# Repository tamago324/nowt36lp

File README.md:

# nowt36lp

horizon プラグインを使ってボトムプレートとトッププレートを生成した

## LICENSE

<br />この 作品 は <a rel="license" href="http://creativecommons.org/licenses/by/4.0/">クリエイティブ・コモンズ 表示 4.0 国際 ライセンス</a>の下に提供されています。

> 帰属—適切なクレジットを表示し、ライセンスへのリンクを提供し、変更が行われたかどうかを示す必要があります。

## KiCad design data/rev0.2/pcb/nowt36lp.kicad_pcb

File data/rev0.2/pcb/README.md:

## 発注するデータの作成方法

horizon のプラグインを使って、発注するためのデータを作成

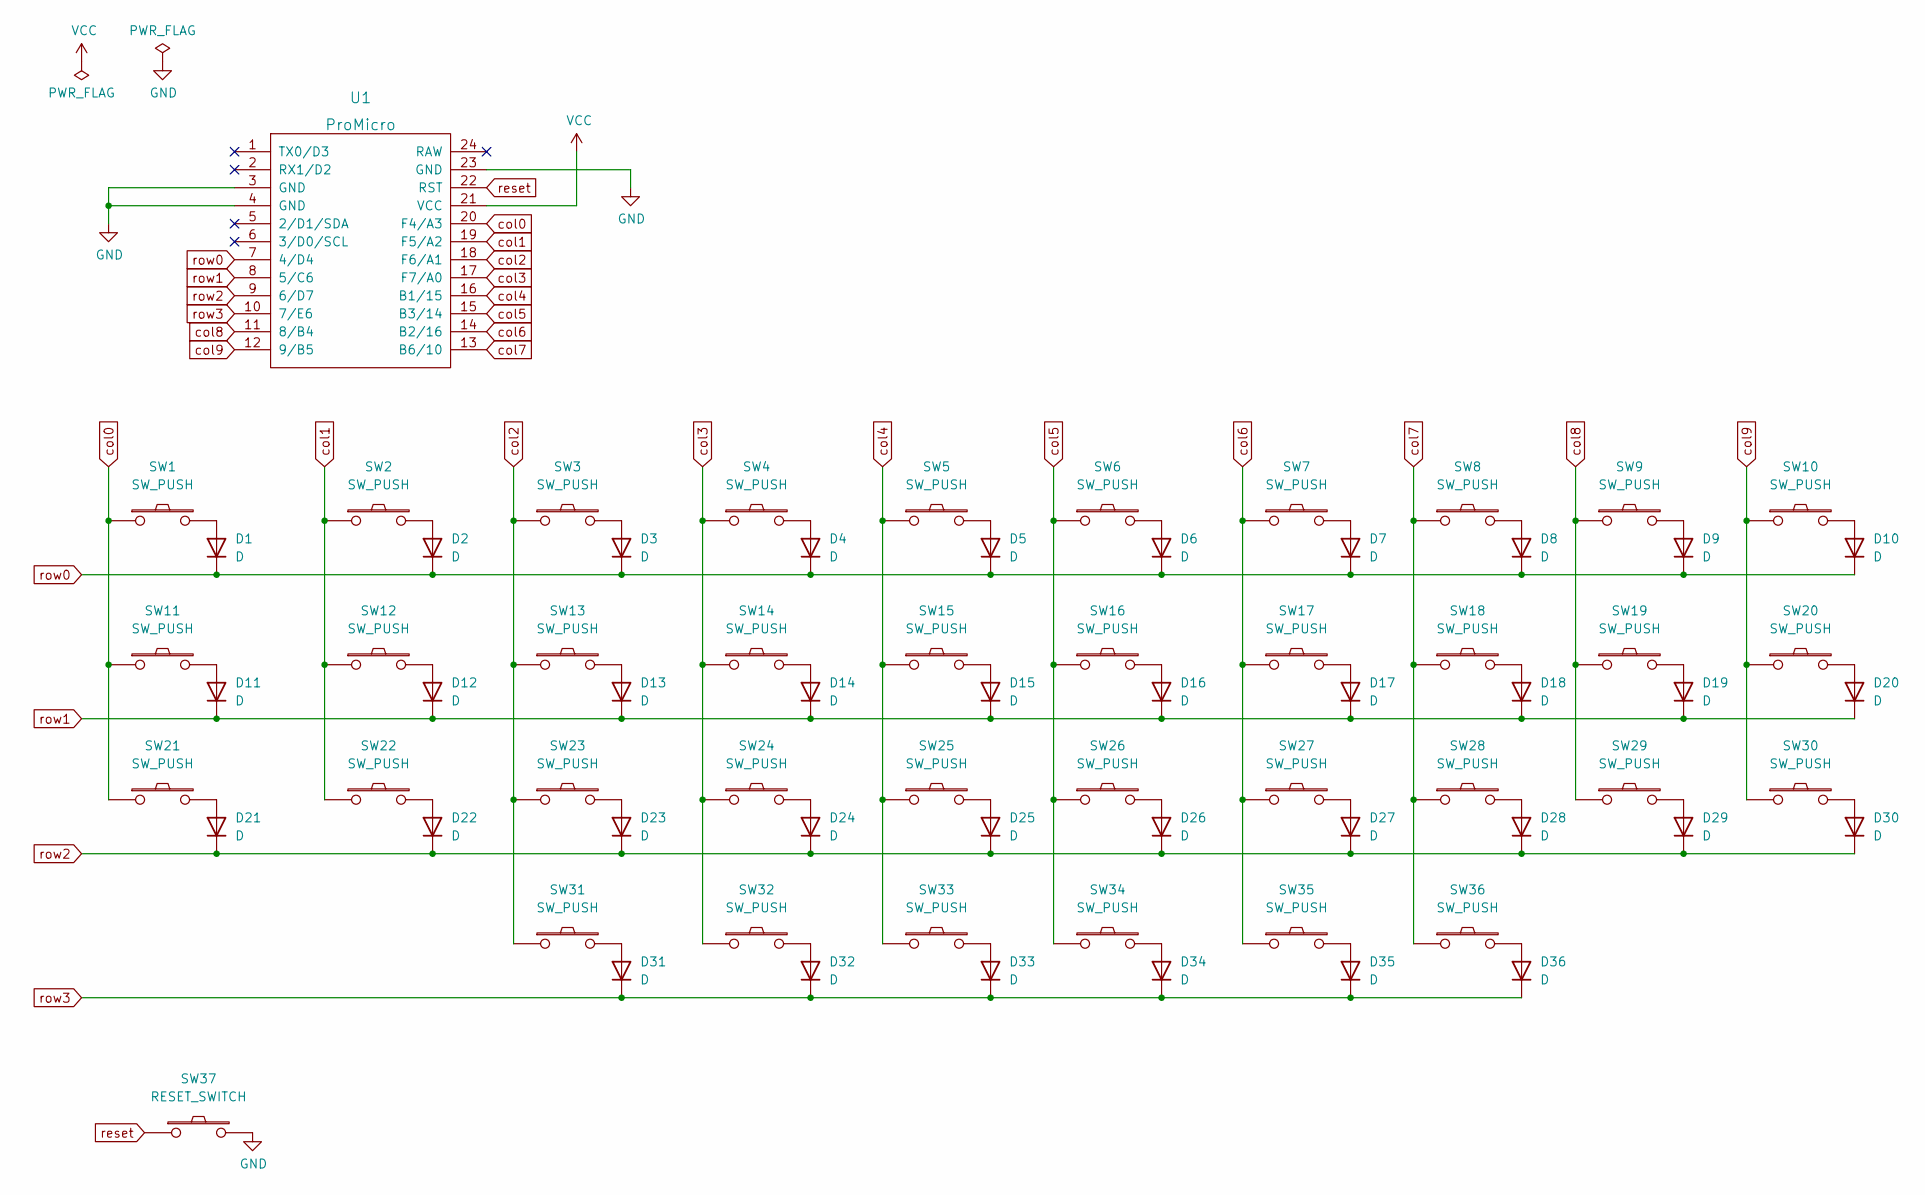
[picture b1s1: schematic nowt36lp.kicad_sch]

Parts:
D1, D2, D3, D4, D5, D6, D7, D8, D9, D10, D11, D12, D13, D14, D15, D16, D17, D18, D19, D20, D21, D22, D23, D24, D25, D26, D27, D28, D29, D30, D31, D32, D33, D34, D35, D36: D; Diode_SMD
SW1, SW2, SW3, SW4, SW5, SW6, SW7, SW8, SW9, SW10, SW11, SW12, SW13, SW14, SW15, SW16, SW17, SW18, SW19, SW20, SW21, SW22, SW23, SW24, SW25, SW26, SW27, SW28, SW29, SW30, SW31, SW32, SW33, SW34, SW35, SW36: SW_PUSH; SW_Choc
SW37: RESET_SWITCH; TVAF17-WFC-R_mods
U1: ProMicro; ProMicro_v3.5_mods

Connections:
GND: SW37.2, U1.3 (GND), U1.4 (GND), U1.23 (GND)
unnamed: D1.2 (A), SW1.2
unnamed: D2.2 (A), SW2.2
unnamed: D3.2 (A), SW3.2
unnamed: D4.2 (A), SW4.2
unnamed: D5.2 (A), SW5.2
unnamed: D6.2 (A), SW6.2
unnamed: D7.2 (A), SW7.2
unnamed: D8.2 (A), SW8.2
unnamed: D9.2 (A), SW9.2
unnamed: D10.2 (A), SW10.2
unnamed: D11.2 (A), SW11.2
unnamed: D12.2 (A), SW12.2
unnamed: D13.2 (A), SW13.2
unnamed: D14.2 (A), SW14.2
unnamed: D15.2 (A), SW15.2
unnamed: D16.2 (A), SW16.2
unnamed: D17.2 (A), SW17.2
unnamed: D18.2 (A), SW18.2
unnamed: D19.2 (A), SW19.2
unnamed: D20.2 (A), SW20.2
unnamed: D21.2 (A), SW21.2
unnamed: D22.2 (A), SW22.2
unnamed: D23.2 (A), SW23.2
unnamed: D24.2 (A), SW24.2
unnamed: D25.2 (A), SW25.2
unnamed: D26.2 (A), SW26.2
unnamed: D27.2 (A), SW27.2
unnamed: D28.2 (A), SW28.2
unnamed: D29.2 (A), SW29.2
unnamed: D30.2 (A), SW30.2
unnamed: D31.2 (A), SW31.2
unnamed: D32.2 (A), SW32.2
unnamed: D33.2 (A), SW33.2
unnamed: D34.2 (A), SW34.2
unnamed: D35.2 (A), SW35.2
unnamed: D36.2 (A), SW36.2
VCC: U1.21 (VCC)
col0: SW1.1, SW11.1, SW21.1, U1.20 (F4/A3)
col1: SW2.1, SW12.1, SW22.1, U1.19 (F5/A2)
col2: SW3.1, SW13.1, SW23.1, SW31.1, U1.18 (F6/A1)
col3: SW4.1, SW14.1, SW24.1, SW32.1, U1.17 (F7/A0)
col4: SW5.1, SW15.1, SW25.1, SW33.1, U1.16 (B1/15)
col5: SW6.1, SW16.1, SW26.1, SW34.1, U1.15 (B3/14)
col6: SW7.1, SW17.1, SW27.1, SW35.1, U1.14 (B2/16)
col7: SW8.1, SW18.1, SW28.1, SW36.1, U1.13 (B6/10)
col8: SW9.1, SW19.1, SW29.1, U1.11 (8/B4)
col9: SW10.1, SW20.1, SW30.1, U1.12 (9/B5)
reset: SW37.1, U1.22 (RST)
row0: D1.1 (K), D2.1 (K), D3.1 (K), D4.1 (K), D5.1 (K), D6.1 (K), D7.1 (K), D8.1 (K), D9.1 (K), D10.1 (K), U1.7 (4/D4)
row1: D11.1 (K), D12.1 (K), D13.1 (K), D14.1 (K), D15.1 (K), D16.1 (K), D17.1 (K), D18.1 (K), D19.1 (K), D20.1 (K), U1.8 (5/C6)
row2: D21.1 (K), D22.1 (K), D23.1 (K), D24.1 (K), D25.1 (K), D26.1 (K), D27.1 (K), D28.1 (K), D29.1 (K), D30.1 (K), U1.9 (6/D7)
row3: D31.1 (K), D32.1 (K), D33.1 (K), D34.1 (K), D35.1 (K), D36.1 (K), U1.10 (7/E6)

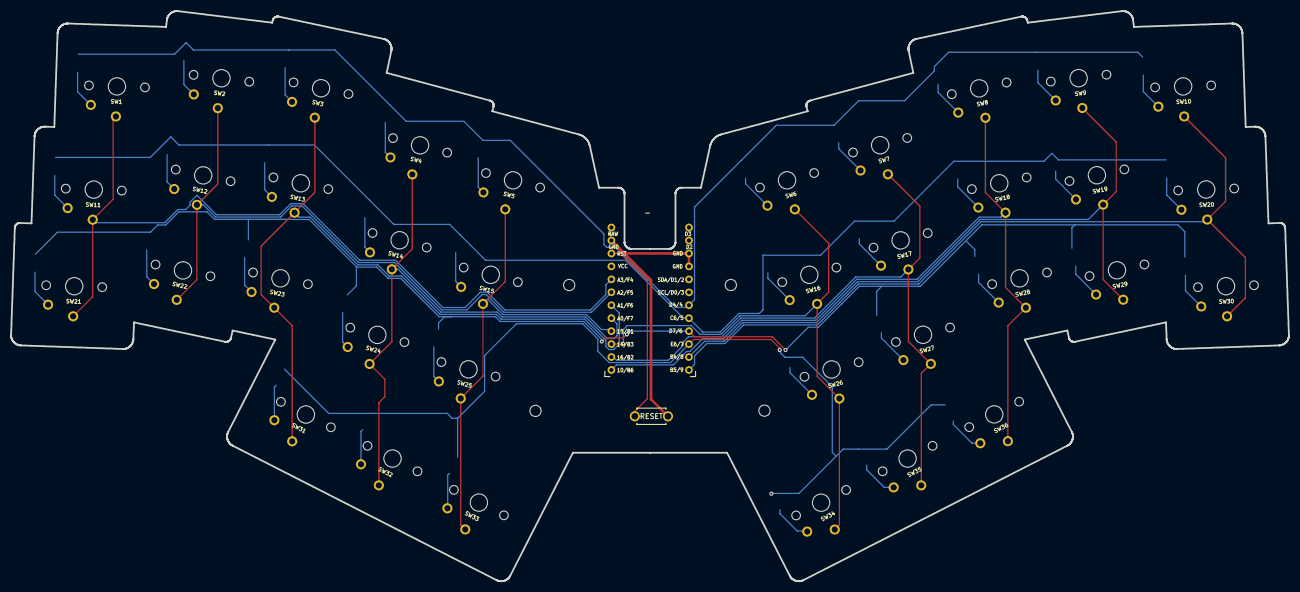
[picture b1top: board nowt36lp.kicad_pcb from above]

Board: 2 copper layers, 250.7 x 111.8 mm, 78 parts (0 on the bottom side), 52 nets.

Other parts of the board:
Ref**: Val**; spacer_m2_2.2mm
Ref**#2, Ref**#3, Ref**#4: Val**; spacer_m2_2.2mm

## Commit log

2022-07-31 init
2022-08-11 ビルドガイドを追加
2022-08-11 ビルドガイドの配置を変更
2022-08-11 画像を追加
2022-08-11 ビルドガイドのパスを修正
2022-08-11 前のビルドガイドを削除
2022-08-11 部品の説明に改行を追加
2022-08-11 fix typo
2022-08-11 ファームウェアのパスを修正
2022-08-11 いらないデータを削除
2022-08-11 ビルドガイド更新
2022-08-11 horizonプラグインの使い方を追加
2022-08-28 update buildguide
2022-09-03 add LICENSE
2022-09-03 ライセンスを CC BY に変更
2022-09-14 画像の追加

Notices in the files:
README.md:
CC BY 4.0
